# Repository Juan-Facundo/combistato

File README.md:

# COMBISTATO :smiley:

Es un circuito electrónico basado en [arduino](https://es.wikipedia.org/wiki/Arduino) para que haga la función de termostato doble accion para controlar frio / calor.

Esta diseñado con un arduino nano con atmega 328.

Su funcionamiento básico es de comandar dos salidas que manejen equipos de frio y calor para mantener la temperatura de lo que se desea controlar. Para ello se puede ajustar:
* Punto de ajuste de trabajo (set point)
* Ajuste de la ventana de accion (histeresis)
* Retardo de reconeccion para frio y calor separados (algunos equipos lo requieren)
* Error: ajuste de calibracion para eliminar el posible error de la medicion.

La presición del aparato depende mayormente del sensensor. En este caso, el fabricante del 18b20 dice que puede tener un error de 0,5 grados centígrados. Otros sensores, se verá.
Tiene la funcion de guardar los valores de ajustes en la memoria eeprom para que sean legibles luego de una desconexión de la alimentación.
Posee la posbilidad de habilitar o deshabilitar el regitro en consola serial.

## La idea:
La idea es poder realizar con poco dinero, una circuito util, de gran versatilidad y bastante fiable.
Se usara sensor digital de tempertatura [ds18b20](https://datasheets.maximintegrated.com/en/ds/DS18B20.pdf), pero puede usarse cualquiera.
En la salida tendrá un modulo de relé doble, con capacidad de 10A. En su idea original, fue diseñado para controla un motocompresor de refrigeración.

## La electrónica:
* Arduino [nano](https://www.arduino.cc/en/Guide/ArduinoNano) con atmega 328
* modulo de relé de 5v con contacto para 10A
* teclado matricial 4x4
* pequeña fuente de alimentación 
* resistores varios
* display [lcd-16x02](https://www.engineersgarage.com/electronic-components/16x2-lcd-module-datasheet)

#### Para hacer:

- Conectar un _buzzer_ y agregar el codigo que falta para las alarmas.
- Desarrollar el codigo para poder configurarlo como dos termostatos separados.

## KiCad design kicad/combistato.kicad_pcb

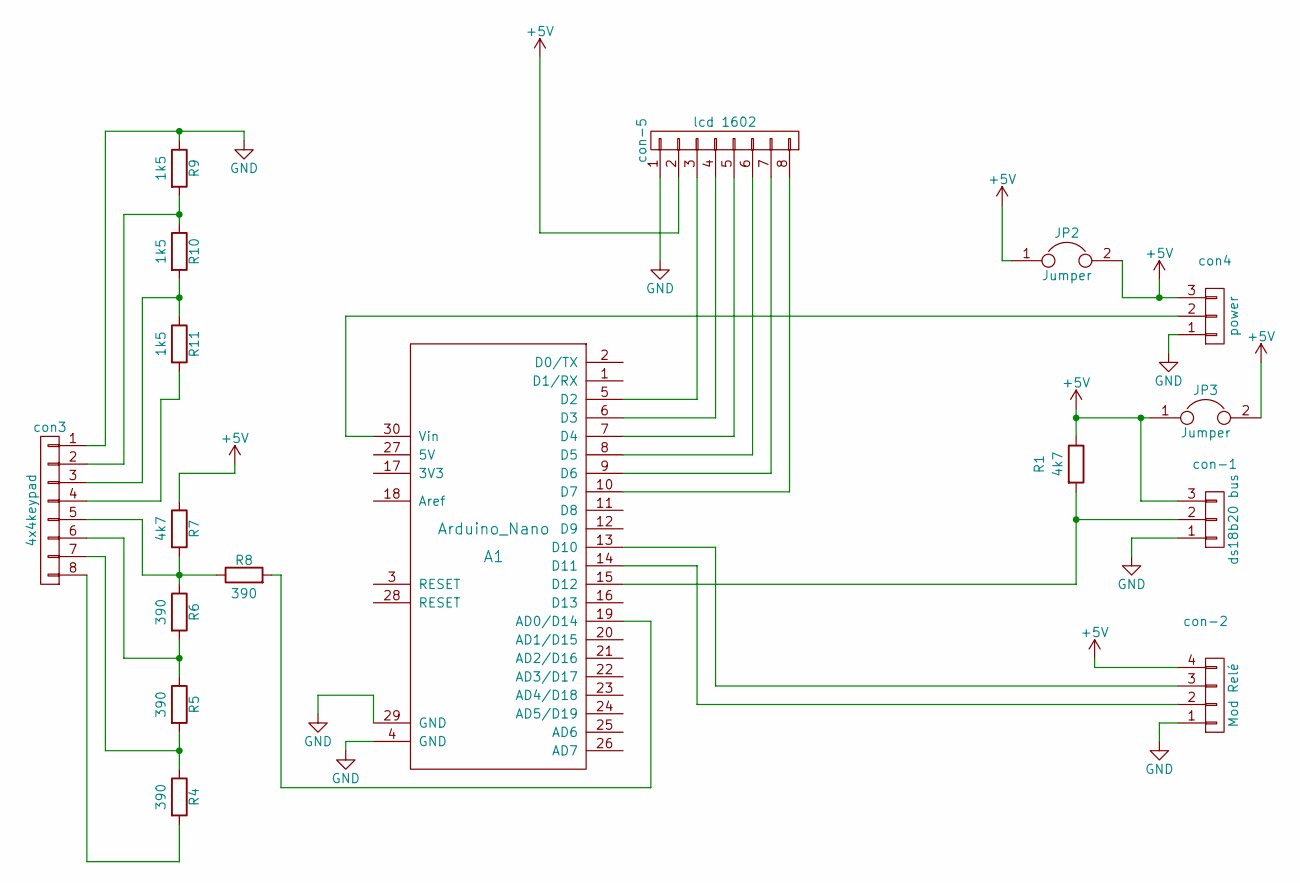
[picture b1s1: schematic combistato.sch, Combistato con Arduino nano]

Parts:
A1: Arduino_Nano; arduino_nano
JP2, JP3: Jumper; R_Axial_DIN0411_L9.9mm_D3.6mm_P12.70mm_Horizontal
R1, R7: 4k7; R_Axial_DIN0411_L9.9mm_D3.6mm_P12.70mm_Horizontal
R4, R5, R6, R8: 390; R_Axial_DIN0411_L9.9mm_D3.6mm_P12.70mm_Horizontal
R9, R10, R11: 1k5; R_Axial_DIN0411_L9.9mm_D3.6mm_P12.70mm_Horizontal
con3: 4x4keypad; Pin_Header_Angled_1x08
con4: power; Pin_Header_Angled_1x03
con-1: ds18b20 bus; Pin_Header_Angled_1x03
con-2: Mod Relé; Pin_Header_Angled_1x04
con-5: lcd 1602; Pin_Header_Angled_1x08

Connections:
+5V: JP2.1, JP2.2, JP3.1, JP3.2, R1.1, R7.1, con4.3, con-1.3, con-2.4, con-5.2
GND: A1.4 (GND), A1.29 (GND), R9.1, con3.1, con4.1, con-1.1, con-2.1, con-5.1
unnamed: A1.5 (D2), con-5.3
unnamed: A1.6 (D3), con-5.4
unnamed: A1.7 (D4), con-5.5
unnamed: A1.8 (D5), con-5.6
unnamed: A1.9 (D6), con-5.7
unnamed: A1.10 (D7), con-5.8
unnamed: A1.13 (D10), con-2.3
unnamed: A1.14 (D11), con-2.2
unnamed: A1.15 (D12), R1.2, con-1.2
unnamed: A1.19 (AD0/D14), R8.2
unnamed: A1.30 (Vin), con4.2
unnamed: R4.1, R5.2, con3.7
unnamed: R4.2, con3.8
unnamed: R5.1, R6.2, con3.6
unnamed: R6.1, R7.2, R8.1, con3.5
unnamed: R9.2, R10.1, con3.2
unnamed: R10.2, R11.1, con3.3
unnamed: R11.2, con3.4

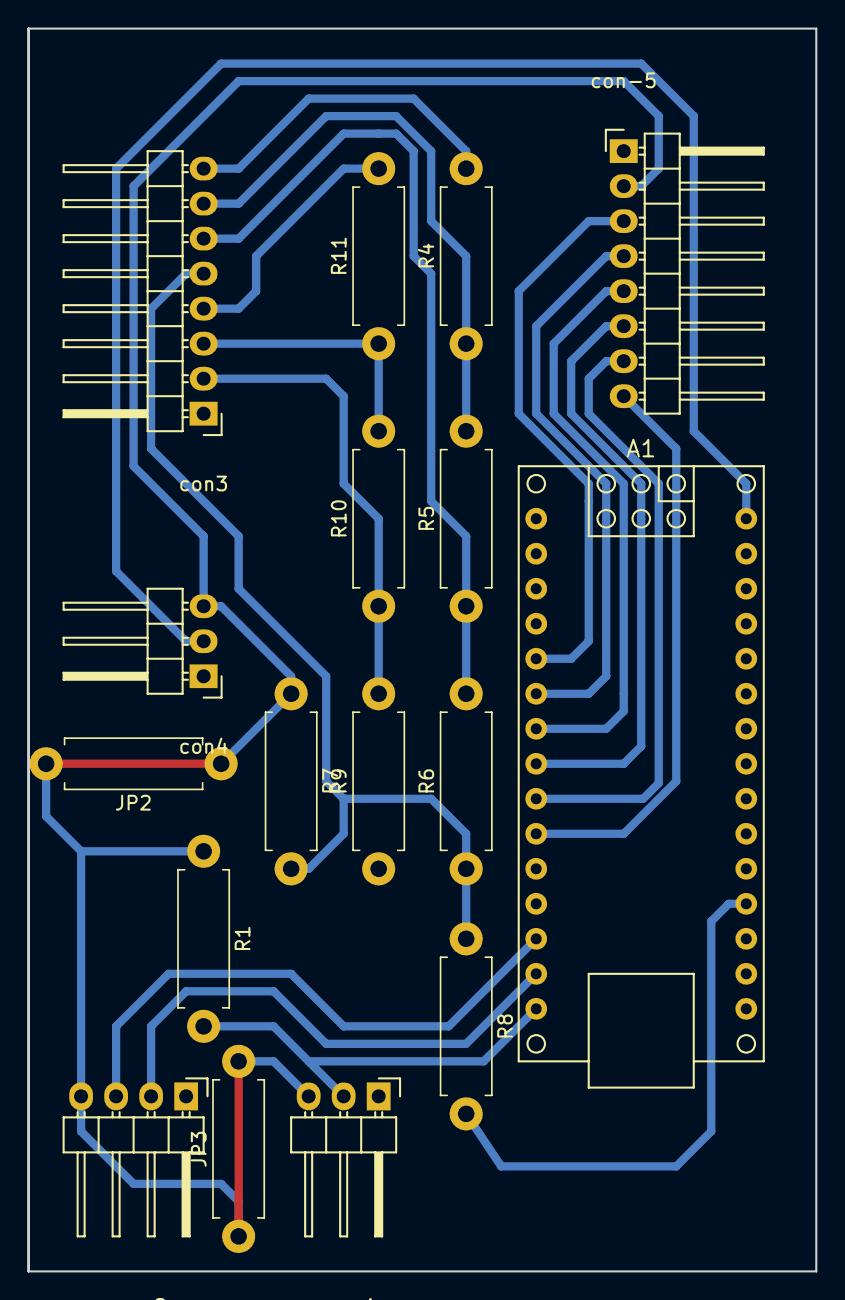
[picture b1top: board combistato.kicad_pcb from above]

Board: 2 copper layers, 57.1 x 90.2 mm, 17 parts (0 on the bottom side), 20 nets.

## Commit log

2019-04-02 primer commit
2019-04-02 editando el readme
2019-04-02 agregando librerias para kicad
2019-04-02 edicion de kicad para diagrama de circuito
2019-04-03 trabajo en pcb, circuitos, etc
2019-04-03 trabajando en pcb, esquema de circuito y otros
